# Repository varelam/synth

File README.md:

# My DIY synth repository includes files for:
- Arduino Code
- Eagle PCB schematics and board
- AutoCAD drawings for Panel
- SolidWorks 3D model
- Pictures and documentation

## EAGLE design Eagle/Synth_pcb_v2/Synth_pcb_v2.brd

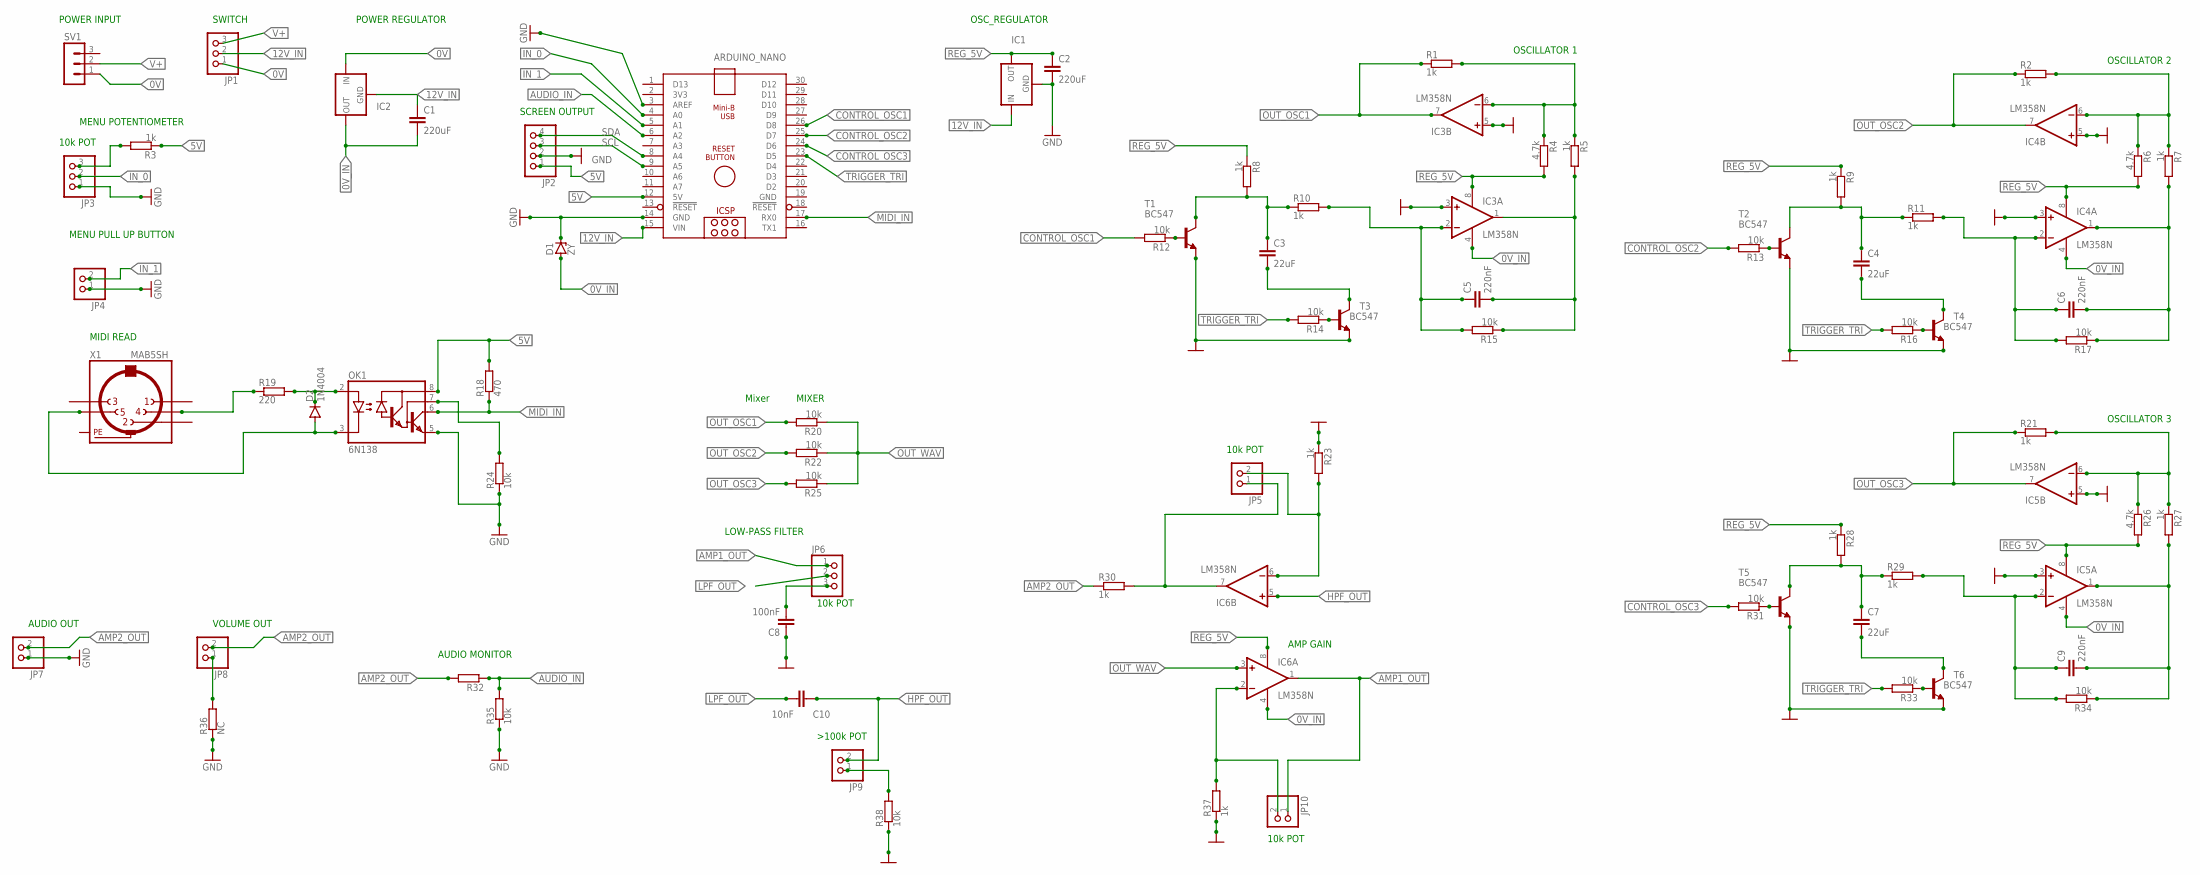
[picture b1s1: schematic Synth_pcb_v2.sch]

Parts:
ARDUINO_NANO: ARDUINO_NANO
C1, C2: 220uF; C2.5-3
C3, C4, C7: 22uF; C2.5-3
C5, C6, C9: 220nF; C2.5-3
C8: 100nF; C2.5-3
C10: 10nF; C2.5-3
D1: ZY; P1Z12
D2: 1N4004; DO41-10
IC1: 78XXS
IC2: 79XXS
IC3, IC4, IC5, IC6: LM358N; DIL08
JP1, JP3, JP6: PINHD-1X3; 1X03
JP2: PINHD-1X4; 1X04
JP4, JP5, JP7, JP8, JP9, JP10: PINHD-1X2; 1X02
OK1: 6N138; DIL08
R1, R2, R3, R5, R7, R8, R9, R10, R11, R21, R23, R27, R28, R29, R30, R32, R37: 1k; 0204/7
R4, R6, R26: 4.7k; 0204/7
R12, R13, R14, R15, R16, R17, R20, R22, R24, R25, R31, R33, R34, R35, R38: 10k; 0204/7
R18: 470; 0204/7
R19: 220; 0204/7
R36: NC; 0204/7
SV1: MA03-1
T1, T2, T3, T4, T5, T6: BC547; TO92
X1: MAB5SH

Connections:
0V: IC2.IN, JP1.1, SV1.1
0V_IN: C1.2, D1.A, IC2.OUT, IC3.4 (V-), IC4.4 (V-), IC5.4 (V-), IC6.4 (V-)
5V: ARDUINO_NANO.12 (5V), JP2.1, OK1.8 (VCC), R3.1, R18.2
12V_IN: ARDUINO_NANO.15 (VIN), C1.1, IC1.IN, IC2.GND, JP1.2
AMP1_OUT: IC6.1 (OUT), JP6.1, JP10.1
AMP2_OUT: JP7.2, JP8.2, R30.1, R32.2
AUDIO_IN: ARDUINO_NANO.6 (A2), R32.1, R35.2
CONTROL_OSC1: ARDUINO_NANO.26 (D8), R12.2
CONTROL_OSC2: ARDUINO_NANO.25 (D7), R13.2
CONTROL_OSC3: ARDUINO_NANO.24 (D6), R31.2
GND: ARDUINO_NANO.3 (AREF), ARDUINO_NANO.14 (GND), ARDUINO_NANO.19 (GND), C2.2, C8.1, D1.C, IC1.GND, IC3.3 (+IN), IC3.5 (+IN), IC4.3 (+IN), IC4.5 (+IN), IC5.3 (+IN), IC5.5 (+IN), JP2.2, JP3.1, JP4.1, JP7.1, OK1.5 (GND), R23.1, R24.1, R35.1, R36.1, R37.1, R38.1, T1.1 (E), T2.1 (E), T3.1 (E), T4.1 (E), T5.1 (E), T6.1 (E)
GND2: JP9.1, R38.2
HPF_OUT: C10.1, IC6.5 (+IN), JP9.2
IN_0: ARDUINO_NANO.4 (A0), JP3.2
IN_1: ARDUINO_NANO.5 (A1), JP4.2
LPF_OUT: C10.2, JP6.2
MIDI_IN: ARDUINO_NANO.17 (RX0), OK1.6 (VO), R18.1
unnamed: D2.A, OK1.3 (C), X1.5
unnamed: IC6.7 (OUT), JP5.1, R30.2
unnamed: D2.C, OK1.2 (A), R19.2
unnamed: R19.1, X1.4
unnamed: OK1.7 (VB), R24.2
unnamed: C3.2, T3.3 (C)
unnamed: JP3.3, R3.2
unnamed: C5.1, IC3.2 (-IN), R10.2, R15.2
unnamed: R12.1, T1.2 (B)
unnamed: R14.1, T3.2 (B)
unnamed: C3.1, R8.2, R10.1, T1.3 (C)
unnamed: C5.2, IC3.1 (OUT), R5.2, R15.1
unnamed: IC3.6 (-IN), R1.2, R4.1, R5.1
unnamed: C4.1, R9.2, R11.1, T2.3 (C)
unnamed: C4.2, T4.3 (C)
unnamed: C6.1, IC4.2 (-IN), R11.2, R17.2
unnamed: C6.2, IC4.1 (OUT), R7.2, R17.1
unnamed: IC4.6 (-IN), R2.2, R6.1, R7.1
unnamed: R13.1, T2.2 (B)
unnamed: R16.1, T4.2 (B)
unnamed: C7.1, R28.2, R29.1, T5.3 (C)
unnamed: C7.2, T6.3 (C)
unnamed: C9.1, IC5.2 (-IN), R29.2, R34.2
unnamed: C9.2, IC5.1 (OUT), R27.2, R34.1
unnamed: IC5.6 (-IN), R21.2, R26.1, R27.1
unnamed: R31.1, T5.2 (B)
unnamed: R33.1, T6.2 (B)
unnamed: IC6.6 (-IN), JP5.2, R23.2
unnamed: IC6.2 (-IN), JP10.2, R37.2
unnamed: C8.2, JP6.3
unnamed: JP8.1, R36.2
OUT_OSC1: IC3.7 (OUT), R1.1, R20.2
OUT_OSC2: IC4.7 (OUT), R2.1, R22.2
OUT_OSC3: IC5.7 (OUT), R21.1, R25.2
OUT_WAV: IC6.3 (+IN), R20.1, R22.1, R25.1
PE: X1.PE, X1.PE@ (PE)
REG_5V: C2.1, IC1.OUT, IC3.8 (V+), IC4.8 (V+), IC5.8 (V+), IC6.8 (V+), R4.2, R6.2, R8.1, R9.1, R26.2, R28.1
SCL: ARDUINO_NANO.9 (A5), JP2.3
SDA: ARDUINO_NANO.8 (A4), JP2.4
TRIGGER_TRI: ARDUINO_NANO.23 (D5), R14.2, R16.2, R33.2
V+: JP1.3, SV1.2

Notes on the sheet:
POWER INPUT
POWER REGULATOR
MIDI READ
MENU POTENTIOMETER
MENU PULL UP BUTTON
SCREEN OUTPUT
OSC_REGULATOR
10k POT
OSCILLATOR 1
OSCILLATOR 2
OSCILLATOR 3
Mixer
LOW-PASS FILTER
MIXER
AMP GAIN
AUDIO OUT
VOLUME OUT
SWITCH
AUDIO MONITOR

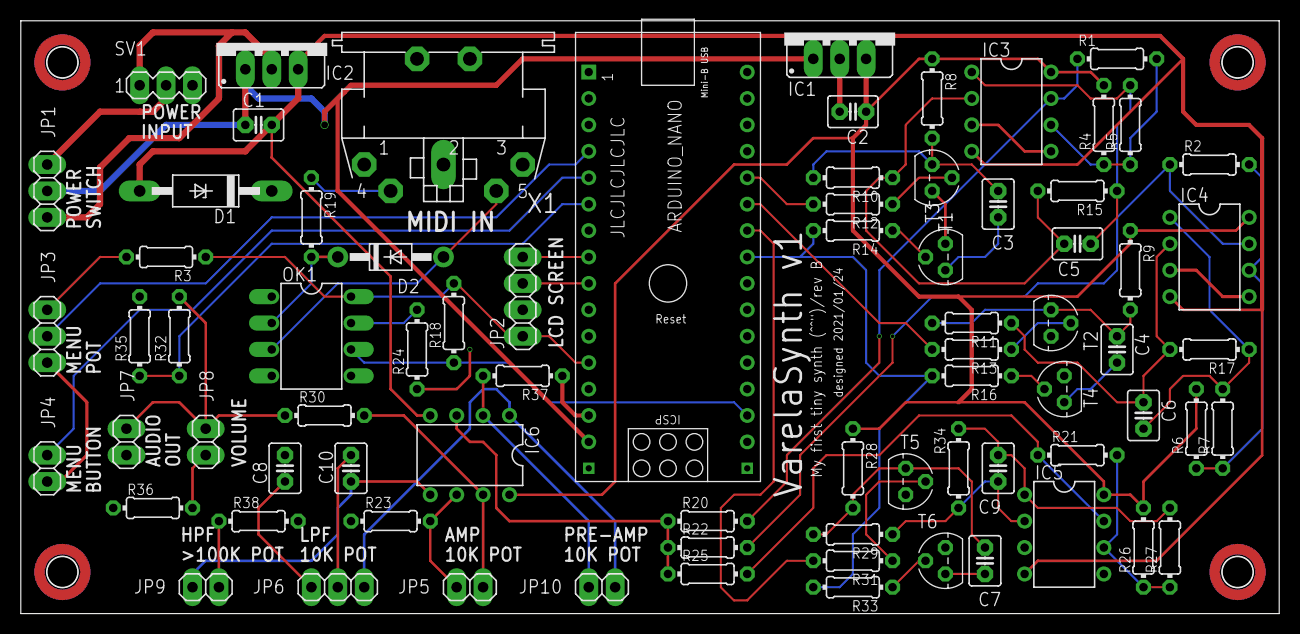
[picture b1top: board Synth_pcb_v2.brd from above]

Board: 2 copper layers, 120.8 x 56.8 mm, 76 parts (0 on the bottom side), 58 nets.

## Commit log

2021-01-14 First Commit in synth design
2021-01-18 Complete schematics, ready to start designing PCB.
2021-01-19 First iteration on PCB design, schematic revised
2021-01-20 Most of the PCB is routed. Revision is needed
2021-01-21 PCB routing complete, ready for revision.
2021-01-24 PCB complete and sent to be manufactured
2021-01-24 Revision B made on time of manufacturing: corrected power schematic
2021-01-27 Started board production and front panel design.
2021-01-28 More effort on developing the front panel...
2021-01-31 First version of front panel drawing.
2021-02-06 Engraved aluminum panel manufacturing order
2021-02-14 Updates in software
2021-04-08 Finished Building and Coding
